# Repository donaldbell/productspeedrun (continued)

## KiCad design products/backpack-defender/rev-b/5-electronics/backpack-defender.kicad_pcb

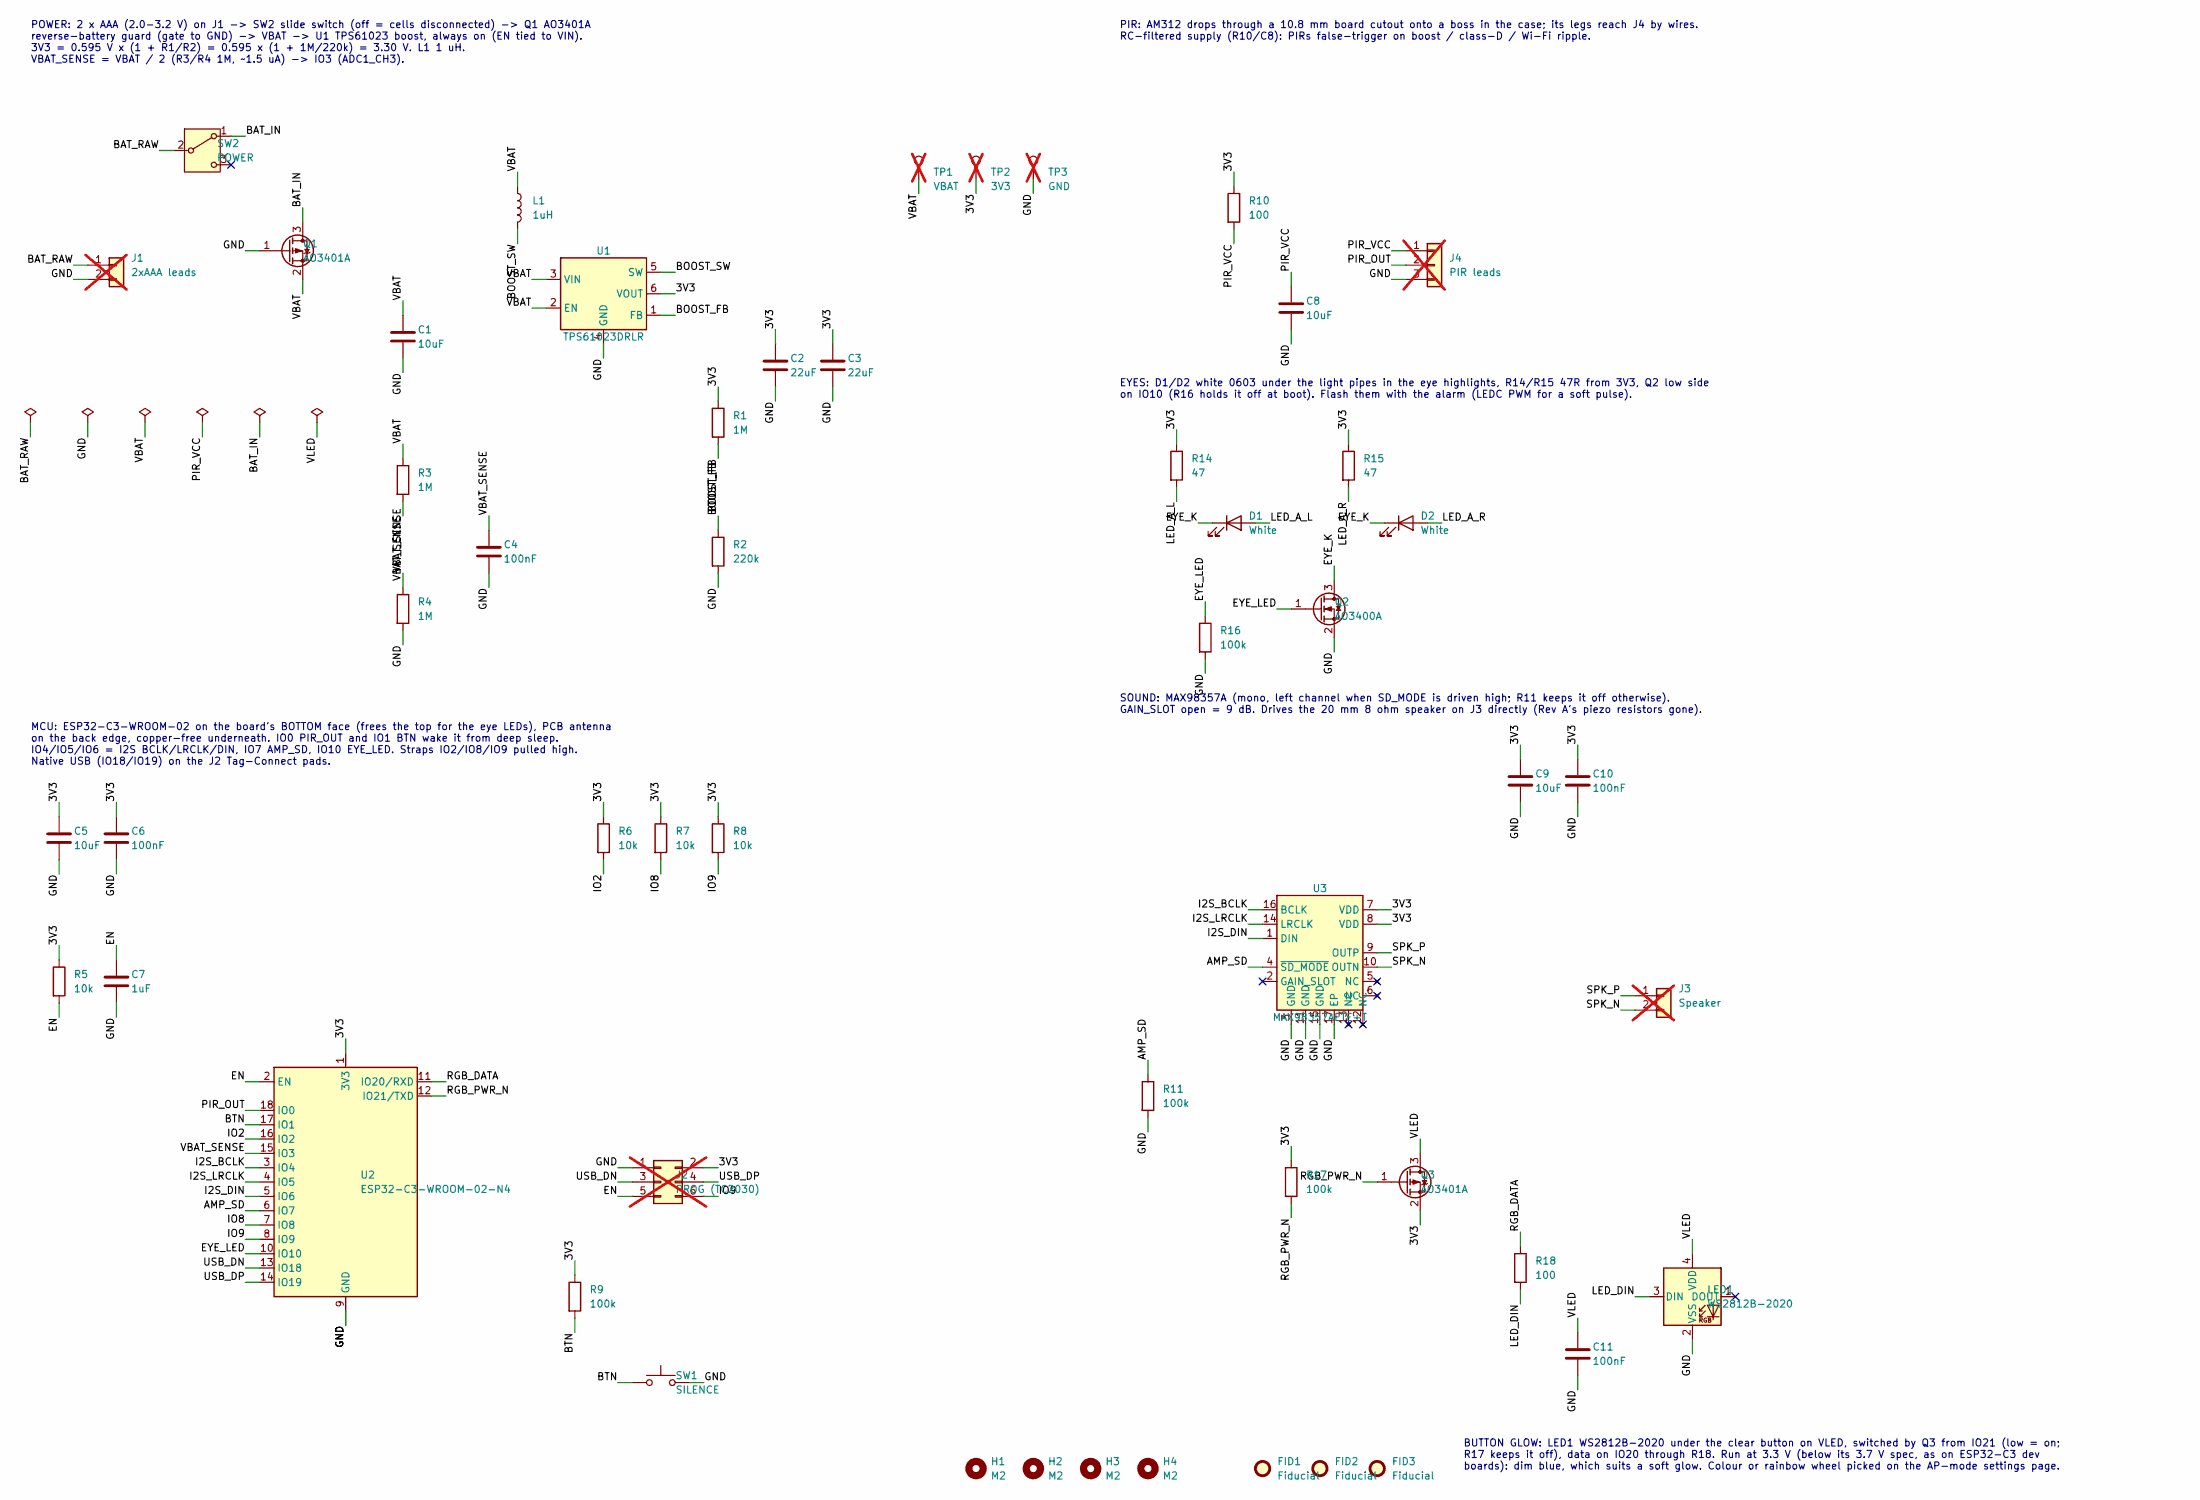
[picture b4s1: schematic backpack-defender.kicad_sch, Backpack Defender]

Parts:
C1, C5, C8, C9: 10uF; C_0805_2012Metric; MPN CL21A106KAYNNNE; LCSC C15850
C2, C3: 22uF; C_0805_2012Metric; MPN CL21A226MAQNNNE; LCSC C45783
C4, C6, C10, C11: 100nF; C_0603_1608Metric; MPN CC0603KRX7R9BB104; LCSC C14663
C7: 1uF; C_0603_1608Metric; MPN CL10A105KB8NNNC; LCSC C15849
D1, D2: White; LED_0603_1608Metric; MPN KT-0603W; LCSC C2290
FID1, FID2, FID3: Fiducial; Fiducial_1mm_Mask2mm
H1, H2, H3, H4: M2; MountingHole_2.2mm_M2
J1: 2xAAA leads; SolderWire-0.25sqmm_1x02_P4.2mm_D0.65mm_OD1.7mm; not fitted
J2: PROG (TC2030); Tag-Connect_TC2030-IDC-NL_2x03_P1.27mm_Vertical; MPN TC2030-IDC-NL (cable); not fitted
J3: Speaker; SolderWire-0.25sqmm_1x02_P4.2mm_D0.65mm_OD1.7mm; not fitted
J4: PIR leads; SolderWire-0.25sqmm_1x03_P4.2mm_D0.65mm_OD1.7mm; not fitted
L1: 1uH; L_Changjiang_FXL0624; MPN FXL0624-1R0-M; LCSC C524602
LED1: WS2812B-2020; LED_WS2812B-2020_PLCC4_2.0x2.0mm; MPN WS2812B-2020; LCSC C965555
Q1, Q3: AO3401A; SOT-23; MPN AO3401A; LCSC C15127
Q2: AO3400A; SOT-23; MPN AO3400A; LCSC C20917
R1, R3, R4: 1M; R_0603_1608Metric; MPN 0603WAF1004T5E; LCSC C22935
R2: 220k; R_0603_1608Metric; MPN 0603WAF2203T5E
R5, R6, R7, R8: 10k; R_0603_1608Metric; MPN 0603WAF1002T5E; LCSC C25804
R9, R11, R16, R17: 100k; R_0603_1608Metric; MPN 0603WAF1003T5E; LCSC C25803
R10, R18: 100; R_0603_1608Metric; MPN 0603WAF1000T5E; LCSC C22775
R14, R15: 47; R_0603_1608Metric; MPN 0603WAF470JT5E; LCSC C23182
SW1: SILENCE; SW_PUSH-12mm; MPN TS-1212-4.3 (12x12x4.3 THT)
SW2: POWER; SW_Slide_SPDT_Angled_CK_OS102011MA1Q; MPN OS102011MA1QN1
TP1: VBAT; TestPoint_Pad_D1.5mm; not fitted
TP2: 3V3; TestPoint_Pad_D1.5mm; not fitted
TP3: GND; TestPoint_Pad_D1.5mm; not fitted
U1: TPS61023DRLR; SOT-563; MPN TPS61023DRLR; LCSC C919459
U2: ESP32-C3-WROOM-02-N4; ESP32-C3-WROOM-02; MPN ESP32-C3-WROOM-02-N4; LCSC C2934560
U3: MAX98357AETE+T; TQFN-16-1EP_3x3mm_P0.5mm_EP1.23x1.23mm_ThermalVias; MPN MAX98357AETE+T

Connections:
/3V3: C2.1, C3.1, C5.1, C6.1, C9.1, C10.1, J2.2, Q3.2 (S), R1.1, R5.1, R6.1, R7.1, R8.1, R9.1, R10.1, R14.1, R15.1, R17.1, TP2.1, U1.6 (VOUT), U2.1 (3V3), U3.7 (VDD), U3.8 (VDD)
/AMP_SD: R11.1, U2.6 (IO7), U3.4 (~SD_MODE)
/BAT_IN: Q1.3 (D), SW2.1 (A)
/BAT_RAW: J1.1, SW2.2 (B)
/BOOST_FB: R1.2, R2.1, U1.1 (FB)
/BOOST_SW: L1.2, U1.5 (SW)
/BTN: R9.2, SW1.1, U2.17 (IO1)
/EN: C7.1, J2.5, R5.2, U2.2 (EN)
/EYE_K: D1.1 (K), D2.1 (K), Q2.3 (D)
/EYE_LED: Q2.1 (G), R16.1, U2.10 (IO10)
/GND: C1.2, C2.2, C3.2, C4.2, C5.2, C6.2, C7.2, C8.2, C9.2, C10.2, C11.2, J1.2, J2.1, J4.3, LED1.2 (VSS), Q1.1 (G), Q2.2 (S), R2.2, R4.2, R11.2, R16.2, SW1.2, TP3.1, U1.4 (GND), U2.9 (GND), U2.19 (GND), U3.3 (GND), U3.11 (GND), U3.15 (GND), U3.17 (EP)
/I2S_BCLK: U2.3 (IO4), U3.16 (BCLK)
/I2S_DIN: U2.5 (IO6), U3.1 (DIN)
/I2S_LRCLK: U2.4 (IO5), U3.14 (LRCLK)
/IO2: R6.2, U2.16 (IO2)
/IO8: R7.2, U2.7 (IO8)
/IO9: J2.6, R8.2, U2.8 (IO9)
/LED_A_L: D1.2 (A), R14.2
/LED_A_R: D2.2 (A), R15.2
/LED_DIN: LED1.3 (DIN), R18.2
/PIR_OUT: J4.2, U2.18 (IO0)
/PIR_VCC: C8.1, J4.1, R10.2
/RGB_DATA: R18.1, U2.11 (IO20/RXD)
/RGB_PWR_N: Q3.1 (G), R17.2, U2.12 (IO21/TXD)
/SPK_N: J3.2, U3.10 (OUTN)
/SPK_P: J3.1, U3.9 (OUTP)
/USB_DN: J2.3, U2.13 (IO18)
/USB_DP: J2.4, U2.14 (IO19)
/VBAT: C1.1, L1.1, Q1.2 (S), R3.1, TP1.1, U1.2 (EN), U1.3 (VIN)
/VBAT_SENSE: C4.1, R3.2, R4.1, U2.15 (IO3)
/VLED: C11.1, LED1.4 (VDD), Q3.3 (D)

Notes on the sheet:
POWER: 2 x AAA (2.0-3.2 V) on J1 -> SW2 slide switch (off = cells disconnected) -> Q1 AO3401A reverse-battery guard (gate to GND) -> VBAT -> U1 TPS61023 boost, always on (EN tied to VIN). 3V3 = 0.595 V x (1 + R1/R2) = 0.595 x (1 + 1M/220k) = 3.30 V. L1 1 uH. VBAT_SENSE = VBAT / 2 (R3/R4 1M, ~1.5 uA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
MCU: ESP32-C3-WROOM-02 on the board's BOTTOM face (frees the top for the eye LEDs), PCB antenna on the back edge, copper-free underneath. IO0 PIR_OUT and IO1 BTN wake it from deep sleep. IO4/IO5/IO6 = I2S BCLK/LRCLK/DIN, IO7 AMP_SD, IO10 EYE_LED. Straps IO2/IO8/IO9 pulled high. Native USB (IO18/IO1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
PIR: AM312 drops through a 10.8 mm board cutout onto a boss in the case; its legs reach J4 by wires. RC-filtered supply (R10/C8): PIRs false-trigger on boost / class-D / Wi-Fi ripple.
EYES: D1/D2 white 0603 under the light pipes in the eye highlights, R14/R15 47R from 3V3, Q2 low side on IO10 (R16 holds it off at boot). Flash them with the alarm (LEDC PWM for a soft pulse).
BUTTON GLOW: LED1 WS2812B-2020 under the clear button on VLED, switched by Q3 from IO21 (low = on; R17 keeps it off), data on IO20 through R18. Run at 3.3 V (below its 3.7 V spec, as on ESP32-C3 dev boards): dim blue, which suits a soft glow. Colour or rainbow wheel picked on the AP-mode settings p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
SOUND: MAX98357A (mono, left channel when SD_MODE is driven high; R11 keeps it off otherwise). GAIN_SLOT open = 9 dB. Drives the 20 mm 8 ohm speaker on J3 directly (Rev A's piezo resistors gone).

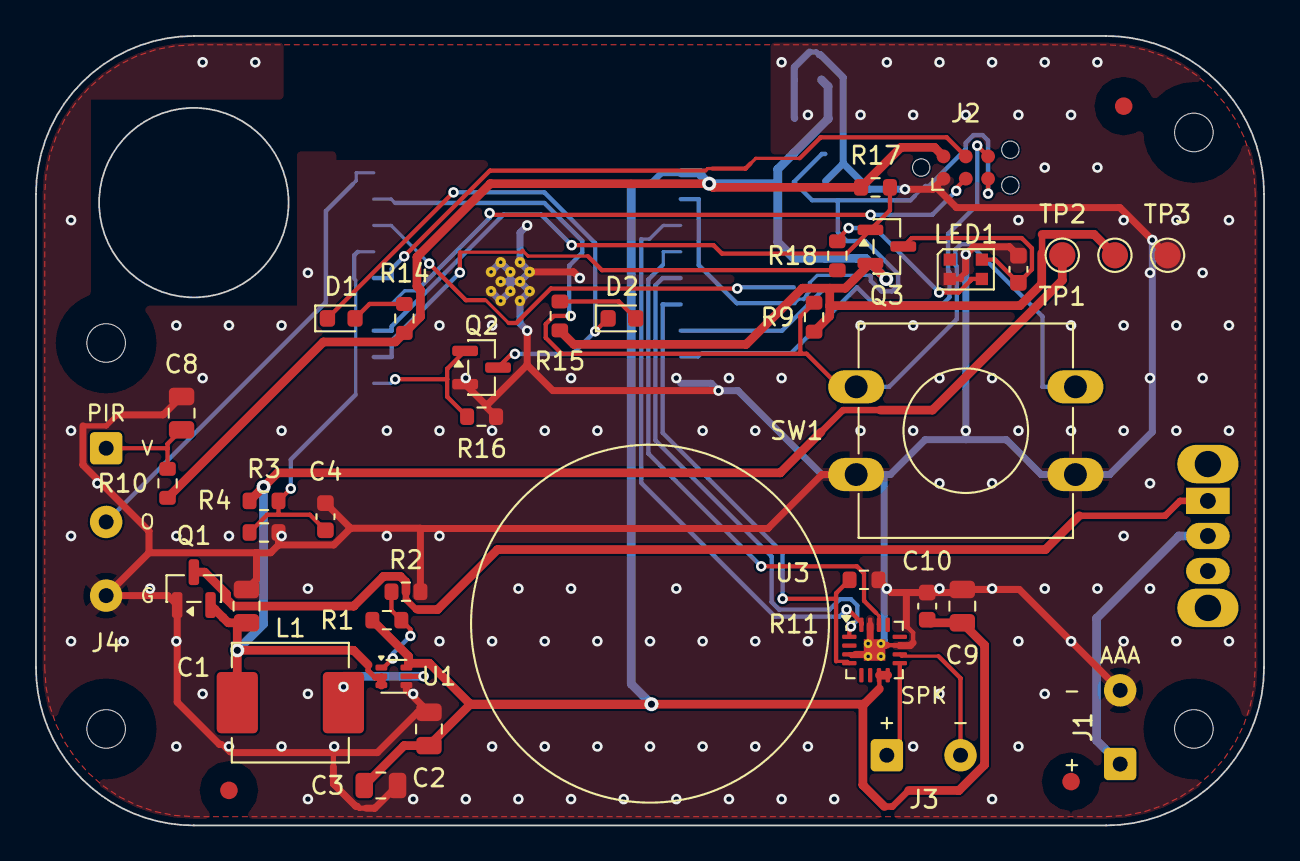
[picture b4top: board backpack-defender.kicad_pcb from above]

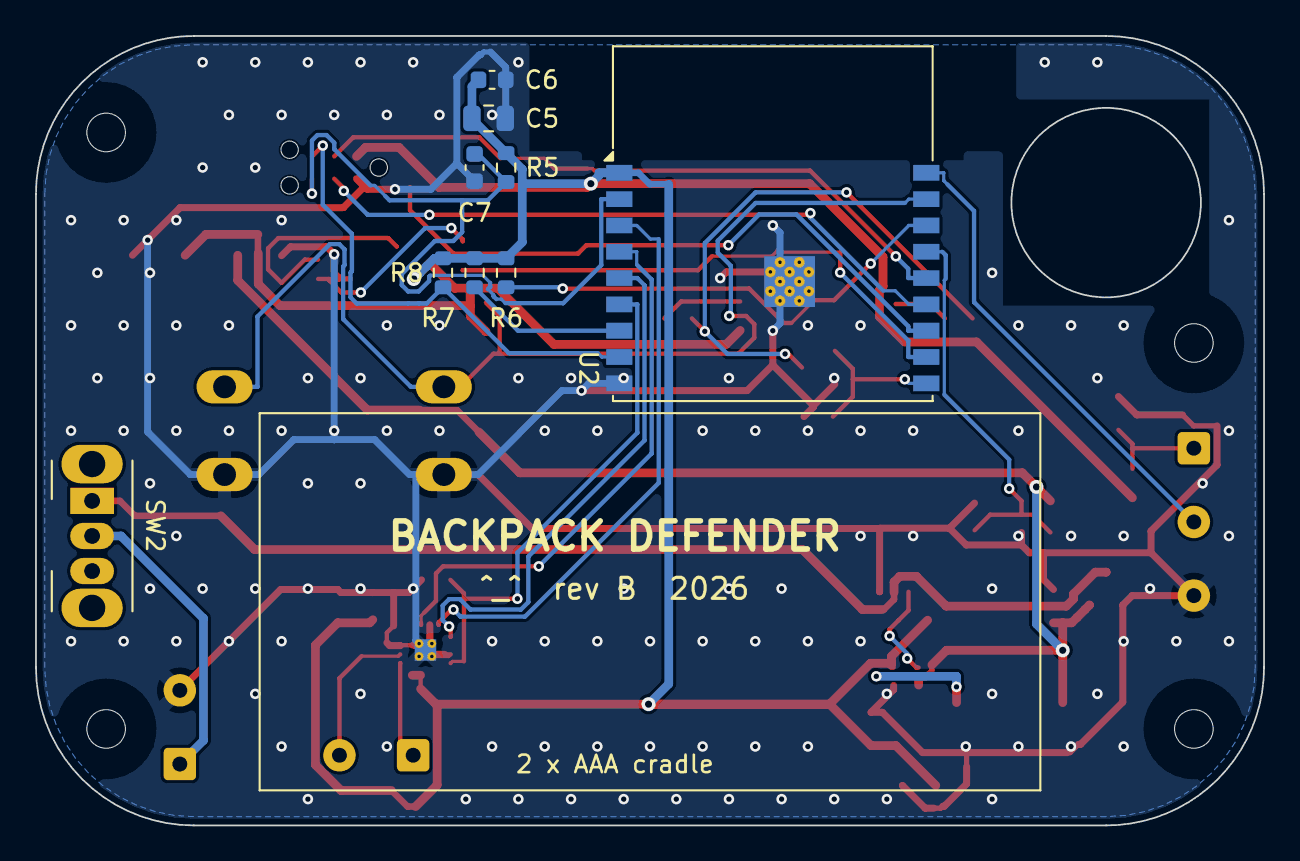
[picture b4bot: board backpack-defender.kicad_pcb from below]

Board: 2 copper layers, 70.0 x 45.0 mm, 53 parts (9 on the bottom side), 31 nets.

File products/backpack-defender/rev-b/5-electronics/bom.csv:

Ref,Qty,Value,Description,Footprint,MPN
C1 C5 C8 C9,4,10uF,"Capacitor, ceramic, 10 uF 25 V X5R 0805",C_0805_2012Metric,CL21A106KAYNNNE
C2 C3,2,22uF,"Capacitor, ceramic, 22 uF 25 V X5R 0805",C_0805_2012Metric,CL21A226MAQNNNE
C4 C6 C10 C11,4,100nF,"Capacitor, ceramic, 100 nF 50 V X7R 0603",C_0603_1608Metric,CC0603KRX7R9BB104
C7,1,1uF,"Capacitor, ceramic, 1 uF 50 V X5R 0603",C_0603_1608Metric,CL10A105KB8NNNC
D1 D2,2,White,"LED white 0603, under the left eye's light pipe",LED_0603_1608Metric,KT-0603W
L1,1,1uH,"Inductor, power, 1 uH, 9 A sat, 7 x 6.6 mm",L_Changjiang_FXL0624,FXL0624-1R0-M
LED1,1,WS2812B-2020,"RGB LED 2 x 2 mm, addressable, under the clear button",LED_WS2812B-2020_PLCC4_2.0x2.0mm,WS2812B-2020
Q1 Q3,2,AO3401A,"P-MOSFET -30 V -4 A SOT-23: reverse-battery guard, drain to the cells, gate to GND",SOT-23,AO3401A
Q2,1,AO3400A,N-MOSFET 30 V 5.7 A SOT-23: switches both eye LEDs from IO10,SOT-23,AO3400A
R1 R3 R4,3,1M,"Resistor, 1 %, 0603, 1M",R_0603_1608Metric,0603WAF1004T5E
R2,1,220k,"Resistor, 1 %, 0603, 220k",R_0603_1608Metric,0603WAF2203T5E
R5 R6 R7 R8,4,10k,"Resistor, 1 %, 0603, 10k",R_0603_1608Metric,0603WAF1002T5E
R9 R11 R16 R17,4,100k,"Resistor, 1 %, 0603, 100k",R_0603_1608Metric,0603WAF1003T5E
R10 R18,2,100,"Resistor, 1 %, 0603, 100",R_0603_1608Metric,0603WAF1000T5E
R14 R15,2,47,"Resistor, 1 %, 0603, 47",R_0603_1608Metric,0603WAF470JT5E
SW1,1,SILENCE,"Tactile switch 12 x 12 x 4.3 mm THT (low profile), under the big silence button",SW_PUSH-12mm,TS-1212-4.3 (12x12x4.3 THT)
SW2,1,POWER,"Slide switch SPDT right-angle THT, 4 mm lever out through the case's right end: disconnects the cells",SW_Slide_SPDT_Angled_CK_OS102011MA1Q,OS102011MA1QN1
U1,1,TPS61023DRLR,"Synchronous boost converter 0.5-5.5 V in, 3.7 A switch, SOT-563",SOT-563,TPS61023DRLR
U2,1,ESP32-C3-WROOM-02-N4,"ESP32-C3 Wi-Fi/BLE module, 4 MB flash, PCB antenna, 18 x 20 x 3.2 mm",ESP32-C3-WROOM-02,ESP32-C3-WROOM-02-N4
U3,1,MAX98357AETE+T,"I2S class-D mono amplifier, TQFN-16 3 x 3 mm",TQFN-16-1EP_3x3mm_P0.5mm_EP1.23x1.23mm_ThermalVias,MAX98357AETE+T
BT1,1,2xAAA cradle,"2 x AAA cells in a cradle in the bottom plate, spring contacts wired to J1",off-board,2 x Keystone-style AAA contact pairs
U4,1,AM312,"Mini PIR motion sensor, dome through the lid, wired to J4",off-board,AM312
LS1,1,Speaker 20 mm 8 ohm,"Micro speaker 20 x 4 mm, 8 ohm 1 W, faces the lid grille on a foam ring, wired to J3",off-board,generic 2004 micro speaker

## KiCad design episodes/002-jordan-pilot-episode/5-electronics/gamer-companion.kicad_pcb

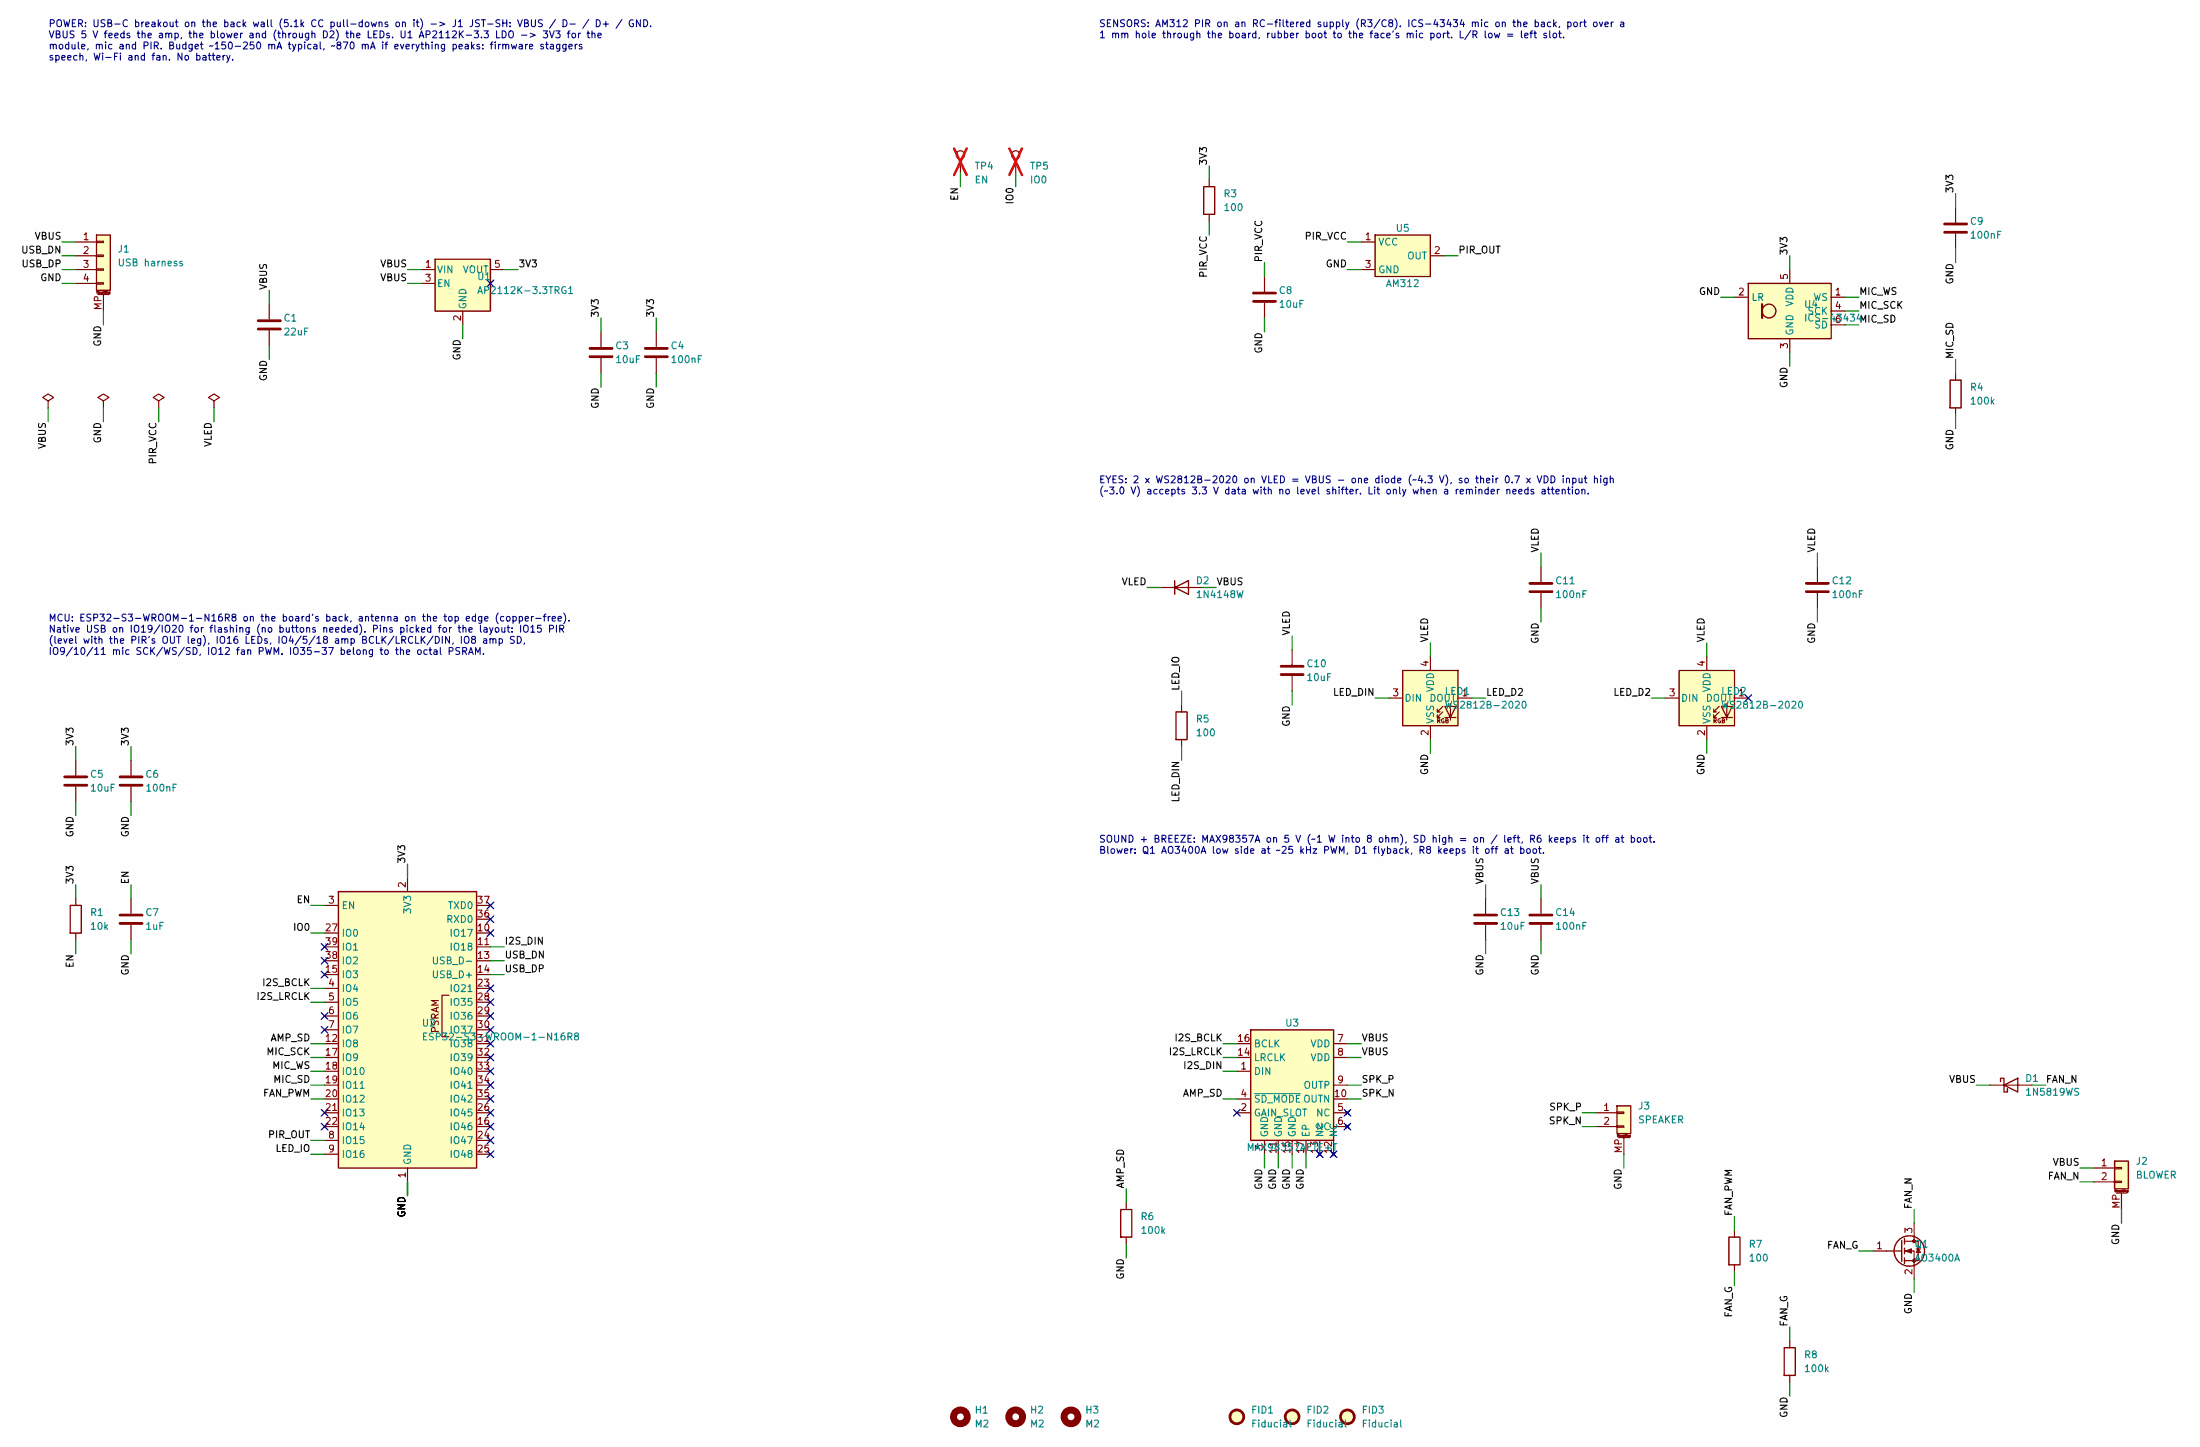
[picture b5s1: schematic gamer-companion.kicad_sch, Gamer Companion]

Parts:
C1: 22uF; C_0805_2012Metric; MPN CL21A226MAQNNNE; LCSC C45783
C3, C5, C8, C10, C13: 10uF; C_0805_2012Metric; MPN CL21A106KAYNNNE; LCSC C15850
C4, C6, C9, C11, C12, C14: 100nF; C_0603_1608Metric; MPN CC0603KRX7R9BB104; LCSC C14663
C7: 1uF; C_0603_1608Metric; MPN CL10A105KB8NNNC; LCSC C15849
D1: 1N5819WS; D_SOD-323; MPN 1N5819WS; LCSC C191023
D2: 1N4148W; D_SOD-123; MPN 1N4148W; LCSC C81598
FID1, FID2, FID3: Fiducial; Fiducial_1mm_Mask2mm
H1, H2, H3: M2; MountingHole_2.2mm_M2
J1: USB harness; JST_SH_SM04B-SRSS-TB_1x04-1MP_P1.00mm_Horizontal; MPN SM04B-SRSS-TB(LF)(SN); LCSC C160390
J2: BLOWER; JST_SH_SM02B-SRSS-TB_1x02-1MP_P1.00mm_Horizontal; MPN SM02B-SRSS-TB(LF)(SN); LCSC C160402
J3: SPEAKER; JST_SH_SM02B-SRSS-TB_1x02-1MP_P1.00mm_Horizontal; MPN SM02B-SRSS-TB(LF)(SN); LCSC C160402
LED1, LED2: WS2812B-2020; LED_WS2812B-2020_PLCC4_2.0x2.0mm; MPN WS2812B-2020; LCSC C965555
Q1: AO3400A; SOT-23; MPN AO3400A; LCSC C20917
R1: 10k; R_0603_1608Metric; MPN 0603WAF1002T5E; LCSC C25804
R3, R5, R7: 100; R_0603_1608Metric; MPN 0603WAF1000T5E; LCSC C22775
R4, R6, R8: 100k; R_0603_1608Metric; MPN 0603WAF1003T5E; LCSC C25803
TP4: EN; TestPoint_Pad_D1.5mm; not fitted
TP5: IO0; TestPoint_Pad_D1.5mm; not fitted
U1: AP2112K-3.3TRG1; SOT-23-5; MPN AP2112K-3.3TRG1; LCSC C51118
U2: ESP32-S3-WROOM-1-N16R8; ESP32-S3-WROOM-1; MPN ESP32-S3-WROOM-1-N16R8; LCSC C2913202
U3: MAX98357AETE+T; TQFN-16-1EP_3x3mm_P0.5mm_EP1.23x1.23mm_ThermalVias; MPN MAX98357AETE+T
U4: ICS-43434; InvenSense_ICS-43434-6_3.5x2.65mm; MPN ICS-43434
U5: AM312; PinHeader_1x03_P2.54mm_Vertical; MPN AM312

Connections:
/3V3: C3.1, C4.1, C5.1, C6.1, C9.1, R1.1, R3.1, U1.5 (VOUT), U2.2 (3V3), U4.5 (VDD)
/AMP_SD: R6.1, U2.12 (IO8), U3.4 (~SD_MODE)
/EN: C7.1, R1.2, TP4.1, U2.3 (EN)
/FAN_G: Q1.1 (G), R7.2, R8.1
/FAN_N: D1.2 (A), J2.2, Q1.3 (D)
/FAN_PWM: R7.1, U2.20 (IO12)
/GND: C1.2, C3.2, C4.2, C5.2, C6.2, C7.2, C8.2, C9.2, C10.2, C11.2, C12.2, C13.2, C14.2, J1.4, J1.MP (MountPin), J2.MP (MountPin), J3.MP (MountPin), LED1.2 (VSS), LED2.2 (VSS), Q1.2 (S), R4.2, R6.2, R8.2, U1.2 (GND), U2.1 (GND), U2.40 (GND), U2.41 (GND), U3.3 (GND), U3.11 (GND), U3.15 (GND), U3.17 (EP), U4.2 (LR), U4.3 (GND), U5.3 (GND)
/I2S_BCLK: U2.4 (IO4), U3.16 (BCLK)
/I2S_DIN: U2.11 (IO18), U3.1 (DIN)
/I2S_LRCLK: U2.5 (IO5), U3.14 (LRCLK)
/IO0: TP5.1, U2.27 (IO0)
/LED_D2: LED1.1 (DOUT), LED2.3 (DIN)
/LED_DIN: LED1.3 (DIN), R5.2
/LED_IO: R5.1, U2.9 (IO16)
/MIC_SCK: U2.17 (IO9), U4.4 (SCK)
/MIC_SD: R4.1, U2.19 (IO11), U4.6 (SD)
/MIC_WS: U2.18 (IO10), U4.1 (WS)
/PIR_OUT: U2.8 (IO15), U5.2 (OUT)
/PIR_VCC: C8.1, R3.2, U5.1 (VCC)
/SPK_N: J3.2, U3.10 (OUTN)
/SPK_P: J3.1, U3.9 (OUTP)
/USB_DN: J1.2, U2.13 (USB_D-)
/USB_DP: J1.3, U2.14 (USB_D+)
/VBUS: C1.1, C13.1, C14.1, D1.1 (K), D2.2 (A), J1.1, J2.1, U1.1 (VIN), U1.3 (EN), U3.7 (VDD), U3.8 (VDD)
/VLED: C10.1, C11.1, C12.1, D2.1 (K), LED1.4 (VDD), LED2.4 (VDD)

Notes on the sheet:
POWER: USB-C breakout on the back wall (5.1k CC pull-downs on it) -> J1 JST-SH: VBUS / D- / D+ / GND. VBUS 5 V feeds the amp, the blower and (through D2) the LEDs. U1 AP2112K-3.3 LDO -> 3V3 for the module, mic and PIR. Budget ~150-250 mA typical, ~870 mA if everything peaks: firmware staggers speec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
MCU: ESP32-S3-WROOM-1-N16R8 on the board's back, antenna on the top edge (copper-free). Native USB on IO19/IO20 for flashing (no buttons needed). Pins picked for the layout: IO15 PIR (level with the PIR's OUT leg), IO16 LEDs, IO4/5/18 amp BCLK/LRCLK/DIN, IO8 amp SD, IO9/10/11 mic SCK/WS/SD, IO12 fa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
SENSORS: AM312 PIR on an RC-filtered supply (R3/C8). ICS-43434 mic on the back, port over a 1 mm hole through the board, rubber boot to the face's mic port. L/R low = left slot.
EYES: 2 x WS2812B-2020 on VLED = VBUS - one diode (~4.3 V), so their 0.7 x VDD input high (~3.0 V) accepts 3.3 V data with no level shifter. Lit only when a reminder needs attention.
SOUND + BREEZE: MAX98357A on 5 V (~1 W into 8 ohm), SD high = on / left, R6 keeps it off at boot. Blower: Q1 AO3400A low side at ~25 kHz PWM, D1 flyback, R8 keeps it off at boot.

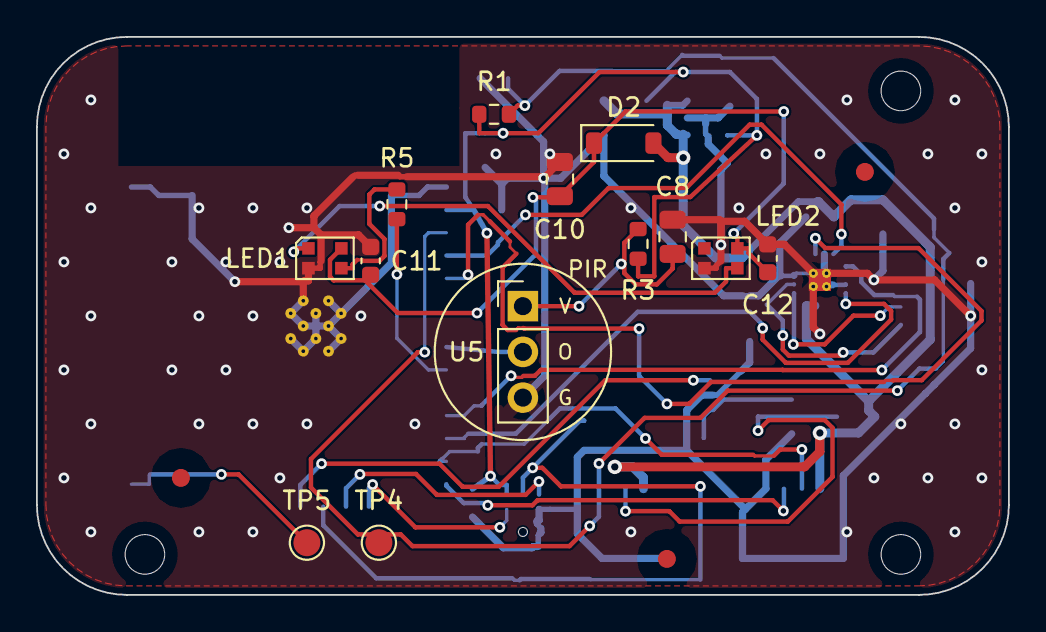
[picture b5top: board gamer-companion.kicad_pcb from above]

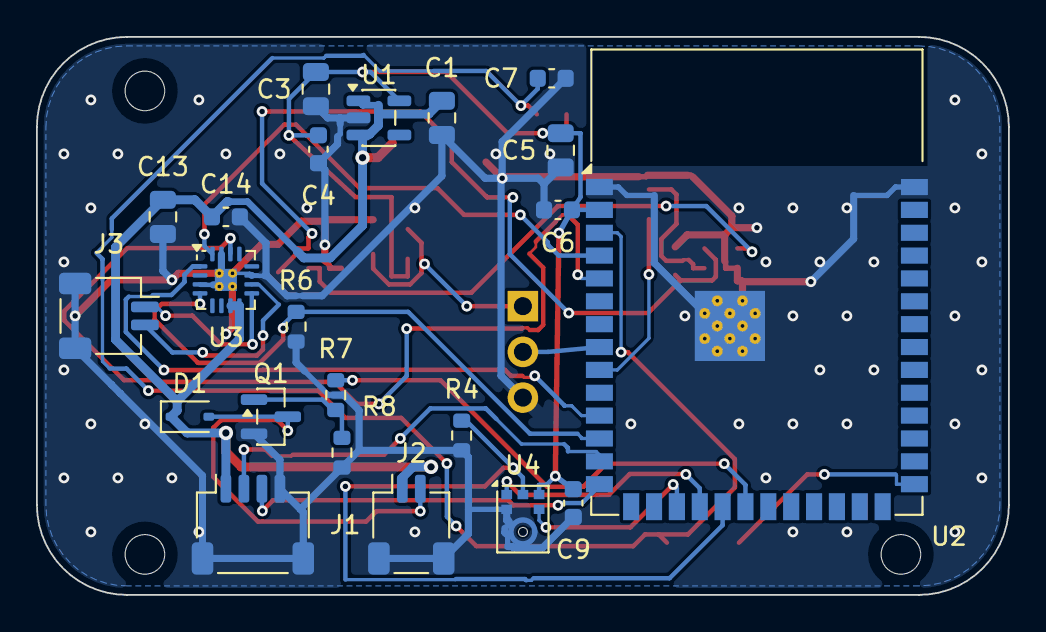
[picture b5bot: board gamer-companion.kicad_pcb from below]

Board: 2 copper layers, 54.0 x 31.0 mm, 41 parts (22 on the bottom side), 25 nets.

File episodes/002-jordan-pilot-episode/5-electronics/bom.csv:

Ref,Qty,Value,Description,Footprint,MPN
C1,1,22uF,"Capacitor, ceramic, 22 uF 25 V X5R 0805",C_0805_2012Metric,CL21A226MAQNNNE
C2 C3 C5 C8 C10 C13,6,10uF,"Capacitor, ceramic, 10 uF 25 V X5R 0805",C_0805_2012Metric,CL21A106KAYNNNE
C4 C6 C9 C11 C12 C14,6,100nF,"Capacitor, ceramic, 100 nF 50 V X7R 0603",C_0603_1608Metric,CC0603KRX7R9BB104
C7,1,1uF,"Capacitor, ceramic, 1 uF 50 V X5R 0603",C_0603_1608Metric,CL10A105KB8NNNC
D1,1,1N5819WS,Schottky 40 V 1 A SOD-323: flyback across the blower,D_SOD-323,1N5819WS
D2,1,1N4148W,"Signal diode, SOD-123: drops VBUS to ~4.3 V so 3.3 V data reads as high",D_SOD-123,1N4148W
J1,1,USB harness,JST-SH 4-pin: VBUS / D- / D+ / GND from the USB-C breakout on the back wall (it carries the 5.1k CC pull-downs),JST_SH_SM04B-SRSS-TB_1x04-1MP_P1.00mm_Horizontal,SM04B-SRSS-TB(LF)(SN)
J2,1,BLOWER,JST-SH 2-pin to the 5 V 3010 blower (+ on pin 1),JST_SH_SM02B-SRSS-TB_1x02-1MP_P1.00mm_Horizontal,SM02B-SRSS-TB(LF)(SN)
J3,1,SPEAKER,JST-SH 2-pin to the 28 mm 8 ohm speaker on the right wall,JST_SH_SM02B-SRSS-TB_1x02-1MP_P1.00mm_Horizontal,SM02B-SRSS-TB(LF)(SN)
LED1 LED2,2,WS2812B-2020,"RGB LED 2 x 2 mm, left eye",LED_WS2812B-2020_PLCC4_2.0x2.0mm,WS2812B-2020
Q1,1,AO3400A,N-MOSFET 30 V 5.7 A SOT-23: low-side PWM switch for the blower,SOT-23,AO3400A
R1 R2,2,10k,"Resistor, 1 %, 0603, 10k",R_0603_1608Metric,0603WAF1002T5E
R3 R5 R7,3,100,"Resistor, 1 %, 0603, 100",R_0603_1608Metric,0603WAF1000T5E
R4 R6 R8,3,100k,"Resistor, 1 %, 0603, 100k",R_0603_1608Metric,0603WAF1003T5E
U1,1,AP2112K-3.3TRG1,"LDO 3.3 V 600 mA, SOT-23-5, EN tied to VIN (always on)",SOT-23-5,AP2112K-3.3TRG1
U2,1,ESP32-S3-WROOM-1-N16R8,"ESP32-S3 Wi-Fi/BLE module, 16 MB flash + 8 MB octal PSRAM (runs ESP-SR on-device), PCB antenna, 18 x 25.5 x 3.1 mm",ESP32-S3-WROOM-1,ESP32-S3-WROOM-1-N16R8
U3,1,MAX98357AETE+T,"I2S class-D mono amplifier on 5 V, TQFN-16 3 x 3 mm",TQFN-16-1EP_3x3mm_P0.5mm_EP1.23x1.23mm_ThermalVias,MAX98357AETE+T
U4,1,ICS-43434,"I2S MEMS microphone, bottom port (over a 1 mm hole in the board), L/R low = left slot",InvenSense_ICS-43434-6_3.5x2.65mm,ICS-43434
U5,1,AM312,Mini PIR motion sensor; dome through the visor,PinHeader_1x03_P2.54mm_Vertical,AM312
BLOWER,1,3010 blower 5 V,"Radial blower 30 x 30 x 10 mm, 5 V ~150 mA, lead re-terminated to JST-SH (J2)",off-board,generic 3010 5 V blower
LS1,1,8 ohm 1 W,"Speaker 28 mm round, 8 ohm 1 W, ~5 mm thick, on the right wall behind the grille (J3)",off-board,generic 28 mm 8 ohm 1 W
USB-C,1,USB-C breakout,"USB-C receptacle breakout with VBUS/D+/D-/GND and 5.1k CC pull-downs, on the back wall (J1)",off-board,generic 4-wire USB-C breakout

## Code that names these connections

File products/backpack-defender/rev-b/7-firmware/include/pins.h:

// GENERATED by scripts/gen_pins.py from ../5-electronics/src/design.py. Do not edit: change the board, then rebuild.
// Every PIN_* can be overridden with a build flag (-DPIN_RGB_DATA=8 for a plain ESP32-C3 dev board).
#pragma once

#define BOARD_NAME "Backpack Defender Rev B"

// PIR_OUT: to J4.2; can wake from deep sleep
#ifndef PIN_PIR_OUT
#define PIN_PIR_OUT 0
#endif
#define PIN_PIR_OUT_PULLUP 0
#define PIN_PIR_OUT_PULLDOWN 0

// BTN: pull-up R9 100k; to SW1.1; can wake from deep sleep
#ifndef PIN_BTN
#define PIN_BTN 1
#endif
#define PIN_BTN_PULLUP 1
#define PIN_BTN_PULLDOWN 0

// IO2: pull-up R6 10k; strapping pin; can wake from deep sleep
#ifndef PIN_IO2
#define PIN_IO2 2
#endif
#define PIN_IO2_PULLUP 1
#define PIN_IO2_PULLDOWN 0

// VBAT_SENSE: pull-down R4 1M; to C4.1, R3.2; can wake from deep sleep
#ifndef PIN_VBAT_SENSE
#define PIN_VBAT_SENSE 3
#endif
#define PIN_VBAT_SENSE_PULLUP 0
#define PIN_VBAT_SENSE_PULLDOWN 1

// I2S_BCLK: to U3.16; can wake from deep sleep
#ifndef PIN_I2S_BCLK
#define PIN_I2S_BCLK 4
#endif
#define PIN_I2S_BCLK_PULLUP 0
#define PIN_I2S_BCLK_PULLDOWN 0

// I2S_LRCLK: to U3.14; can wake from deep sleep
#ifndef PIN_I2S_LRCLK
#define PIN_I2S_LRCLK 5
#endif
#define PIN_I2S_LRCLK_PULLUP 0
#define PIN_I2S_LRCLK_PULLDOWN 0

// I2S_DIN: to U3.1
#ifndef PIN_I2S_DIN
#define PIN_I2S_DIN 6
#endif
#define PIN_I2S_DIN_PULLUP 0
#define PIN_I2S_DIN_PULLDOWN 0

// AMP_SD: pull-down R11 100k; to U3.4
#ifndef PIN_AMP_SD
#define PIN_AMP_SD 7
#endif
#define PIN_AMP_SD_PULLUP 0
#define PIN_AMP_SD_PULLDOWN 1

// IO8: pull-up R7 10k; strapping pin
#ifndef PIN_IO8
#define PIN_IO8 8
#endif
#define PIN_IO8_PULLUP 1
#define PIN_IO8_PULLDOWN 0

// IO9: pull-up R8 10k; to J2.6; strapping pin
#ifndef PIN_IO9
#define PIN_IO9 9
#endif
#define PIN_IO9_PULLUP 1
#define PIN_IO9_PULLDOWN 0

// EYE_LED: pull-down R16 100k; to Q2.1
#ifndef PIN_EYE_LED
#define PIN_EYE_LED 10
#endif
#define PIN_EYE_LED_PULLUP 0
#define PIN_EYE_LED_PULLDOWN 1

// USB_DN: to J2.3
#ifndef PIN_USB_DN
#define PIN_USB_DN 18
#endif
#define PIN_USB_DN_PULLUP 0
#define PIN_USB_DN_PULLDOWN 0

// USB_DP: to J2.4
#ifndef PIN_USB_DP
#define PIN_USB_DP 19
#endif
#define PIN_USB_DP_PULLUP 0
#define PIN_USB_DP_PULLDOWN 0

// RGB_DATA: to R18.1
#ifndef PIN_RGB_DATA
#define PIN_RGB_DATA 20
#endif
#define PIN_RGB_DATA_PULLUP 0
#define PIN_RGB_DATA_PULLDOWN 0

// RGB_PWR_N: pull-up R17 100k; to Q3.1
#ifndef PIN_RGB_PWR_N
#define PIN_RGB_PWR_N 21
#endif
#define PIN_RGB_PWR_N_PULLUP 1
#define PIN_RGB_PWR_N_PULLDOWN 0

// VBAT_SENSE = VBAT x 1e+06 / (1e+06 + 1e+06): multiply the pin voltage by this to get VBAT
#define VBAT_SENSE_RATIO 2.0000f

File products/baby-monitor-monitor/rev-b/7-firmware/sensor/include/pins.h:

// GENERATED by ../common/scripts/gen_pins.py from ../../5-electronics/sensor/src/design.py. Do not edit: change the board, then rebuild.
// pad table cross-checked against KiCad's ESP32-C6-MINI-1 symbol (U3, RF_Module:ESP32-C6-MINI-1).
// Every PIN_* can be overridden with a build flag (the devkit envs in platformio.ini do).
#pragma once

#define BOARD_NAME "Baby Monitor Monitor: Sensor"
#define BOARD_KEY "sensor"

// VBAT_SENSE: pull-down R6 1M; to C5.1, R5.2; LP GPIO (can wake from deep sleep); ADC1 ch0
#ifndef PIN_VBAT_SENSE
#define PIN_VBAT_SENSE 0
#endif
#define PIN_VBAT_SENSE_PULLUP 0
#define PIN_VBAT_SENSE_PULLDOWN 1

// MIC_SD: to U4.6; LP GPIO (can wake from deep sleep); ADC1 ch2
#ifndef PIN_MIC_SD
#define PIN_MIC_SD 2
#endif
#define PIN_MIC_SD_PULLUP 0
#define PIN_MIC_SD_PULLDOWN 0

// LED_IO: to R9.1; LP GPIO (can wake from deep sleep); ADC1 ch3
#ifndef PIN_LED_IO
#define PIN_LED_IO 3
#endif
#define PIN_LED_IO_PULLUP 0
#define PIN_LED_IO_PULLDOWN 0

// MIC_SCK: to U4.4; strapping pin; LP GPIO (can wake from deep sleep); ADC1 ch4
#ifndef PIN_MIC_SCK
#define PIN_MIC_SCK 4
#endif
#define PIN_MIC_SCK_PULLUP 0
#define PIN_MIC_SCK_PULLDOWN 0

// MIC_WS: to U4.1; strapping pin; LP GPIO (can wake from deep sleep); ADC1 ch5
#ifndef PIN_MIC_WS
#define PIN_MIC_WS 5
#endif
#define PIN_MIC_WS_PULLUP 0
#define PIN_MIC_WS_PULLDOWN 0

// BAR_IO: to R10.1; LP GPIO (can wake from deep sleep); ADC1 ch6
#ifndef PIN_BAR_IO
#define PIN_BAR_IO 6
#endif
#define PIN_BAR_IO_PULLUP 0
#define PIN_BAR_IO_PULLDOWN 0

// BTN: to SW1.1, SW3.1; LP GPIO (can wake from deep sleep)
#ifndef PIN_BTN
#define PIN_BTN 7
#endif
#define PIN_BTN_PULLUP 0
#define PIN_BTN_PULLDOWN 0

// IO8: pull-up R8 10k; strapping pin
#ifndef PIN_IO8
#define PIN_IO8 8
#endif
#define PIN_IO8_PULLUP 1
#define PIN_IO8_PULLDOWN 0

// IO9: to TP1.1; strapping pin
#ifndef PIN_IO9
#define PIN_IO9 9
#endif
#define PIN_IO9_PULLUP 0
#define PIN_IO9_PULLDOWN 0

// USB_DN: to J1.A7, J1.B7; native USB D-
#ifndef PIN_USB_DN
#define PIN_USB_DN 12
#endif
#define PIN_USB_DN_PULLUP 0
#define PIN_USB_DN_PULLDOWN 0

// USB_DP: to J1.A6, J1.B6; native USB D+
#ifndef PIN_USB_DP
#define PIN_USB_DP 13
#endif
#define PIN_USB_DP_PULLUP 0
#define PIN_USB_DP_PULLDOWN 0

// CHG_STAT: to U1.1
#ifndef PIN_CHG_STAT
#define PIN_CHG_STAT 21
#endif
#define PIN_CHG_STAT_PULLUP 0
#define PIN_CHG_STAT_PULLDOWN 0

// VBAT_SENSE = VBAT x 1e+06 / (1e+06 + 1e+06): multiply the pin voltage by this to get VBAT
#define VBAT_SENSE_RATIO 2.0000f

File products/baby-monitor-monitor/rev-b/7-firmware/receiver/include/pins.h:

// GENERATED by ../common/scripts/gen_pins.py from ../../5-electronics/receiver/src/design.py. Do not edit: change the board, then rebuild.
// pad table cross-checked against KiCad's ESP32-C6-MINI-1 symbol (U3, RF_Module:ESP32-C6-MINI-1).
// Every PIN_* can be overridden with a build flag (the devkit envs in platformio.ini do).
#pragma once

#define BOARD_NAME "Baby Monitor Monitor: Receiver"
#define BOARD_KEY "receiver"

// VBAT_SENSE: pull-down R3 1M; to C4.1, R2.2; LP GPIO (can wake from deep sleep); ADC1 ch0
#ifndef PIN_VBAT_SENSE
#define PIN_VBAT_SENSE 0
#endif
#define PIN_VBAT_SENSE_PULLUP 0
#define PIN_VBAT_SENSE_PULLDOWN 1

// CHG_STAT: to U1.1; LP GPIO (can wake from deep sleep); ADC1 ch1
#ifndef PIN_CHG_STAT
#define PIN_CHG_STAT 1
#endif
#define PIN_CHG_STAT_PULLUP 0
#define PIN_CHG_STAT_PULLDOWN 0

// MOT_PWM: pull-down R6 100k; to Q1.1; LP GPIO (can wake from deep sleep); ADC1 ch2
#ifndef PIN_MOT_PWM
#define PIN_MOT_PWM 2
#endif
#define PIN_MOT_PWM_PULLUP 0
#define PIN_MOT_PWM_PULLDOWN 1

// LED_IO: to LED1.3; LP GPIO (can wake from deep sleep); ADC1 ch6
#ifndef PIN_LED_IO
#define PIN_LED_IO 6
#endif
#define PIN_LED_IO_PULLUP 0
#define PIN_LED_IO_PULLDOWN 0

// LINK_IO: to R7.1; LP GPIO (can wake from deep sleep)
#ifndef PIN_LINK_IO
#define PIN_LINK_IO 7
#endif
#define PIN_LINK_IO_PULLUP 0
#define PIN_LINK_IO_PULLDOWN 0

// IO8: pull-up R5 10k; strapping pin
#ifndef PIN_IO8
#define PIN_IO8 8
#endif
#define PIN_IO8_PULLUP 1
#define PIN_IO8_PULLDOWN 0

// IO9: to TP1.1; strapping pin
#ifndef PIN_IO9
#define PIN_IO9 9
#endif
#define PIN_IO9_PULLUP 0
#define PIN_IO9_PULLDOWN 0

// USB_DN: to TP3.1; native USB D-
#ifndef PIN_USB_DN
#define PIN_USB_DN 12
#endif
#define PIN_USB_DN_PULLUP 0
#define PIN_USB_DN_PULLDOWN 0

// USB_DP: to TP2.1; native USB D+
#ifndef PIN_USB_DP
#define PIN_USB_DP 13
#endif
#define PIN_USB_DP_PULLUP 0
#define PIN_USB_DP_PULLDOWN 0

// VBAT_SENSE = VBAT x 1e+06 / (1e+06 + 1e+06): multiply the pin voltage by this to get VBAT
#define VBAT_SENSE_RATIO 2.0000f
